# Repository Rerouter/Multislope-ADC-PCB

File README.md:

# Multislope-ADC-PCB
High Resolution Multi-slope ADC Kicad Files

Based on Kleinsteins original design as discussed on the EEVBlog Forum

https://www.eevblog.com/forum/metrology/diy-high-resolution-multi-slope-converter/

https://www.eevblog.com/forum/projects/multislope-design/

The goal of the project is to create a low cost multislope ADC with a useable resolution of 6.5 digits or higher.

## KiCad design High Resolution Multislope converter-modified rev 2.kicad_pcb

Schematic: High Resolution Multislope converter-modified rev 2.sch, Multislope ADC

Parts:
C1, C2, C3, C4, C5, C9, C10, C12, C18, C19, C24, C25, C26, C27, C28, C31, C32, C33, C34, C35, C36, C38, C39, C40, C41, C42, C43, C45, C46, C48, C49, C50, C51, C201, C203, C205, C209, C210: 100n; C_0805_2012Metric
C6: 2.2u; C_0805_2012Metric
C7, C8, C20, C22, C23, C44, C202, C204, C206, C207: 100u; CP_Radial_D8.0mm_P3.50mm
C11: 2.2n; C_Rect_L7.2mm_W3.0mm_P5.00mm_FKS2_FKP2_MKS2_MKP2
C13: 4.7u; C_Rect_L7.2mm_W7.2mm_P5.00mm_FKS2_FKP2_MKS2_MKP2
C14, C21, C29: 220p; C_0805_2012Metric
C15: 22p; C_0805_2012Metric
C16, C47: 10n; C_0805_2012Metric
C17: 330p; C_0805_2012Metric
C30, C37: 1n; C_0805_2012Metric
D1, D7: 12V; D_SOD-323
D3, D5, D8, D11, D12, D13, D14, D18, D19, D201, D202: 1N4148; D_SOD-323
D4, D6, D9: 5.6V; D_SOD-323
D15: BAV199; SOT-23; Manufacturer PArt Number BAV199-7-F; Digikey Part Number BAV199-FDICT-ND
FB1, FB35, FB57, FB102, FB103: Ferrite; L_0805_2012Metric; Manufacturer PArt Number MMZ2012Y152BT
J1: UART; PinHeader_1x04_P2.54mm_Vertical
J2: Input; PinHeader_2x05_P2.54mm_Vertical
J3: ICSP6; PinHeader_2x03_P2.54mm_Vertical
J4: ISCP10; PinHeader_2x05_P2.54mm_Vertical
J5: Power; PinHeader_1x05_P2.54mm_Vertical
LSP6: INTX; PinHeader_1x01_P2.54mm_Vertical
LSP7: Input+; PinHeader_1x01_P2.54mm_Vertical
LSP8: Input-; PinHeader_1x01_P2.54mm_Vertical
LSP200: BIAS; PinHeader_1x01_P2.54mm_Vertical
Q1, Q3, Q4, Q5, Q6, Q9: BC856; SOT-23; Manufacturer PArt Number BC857CLT1G
Q2, Q7, Q8: BC847; SOT-23; Manufacturer PArt Number BC847BLT3G
Q$2: MMBFJ310LT1G; SOT-23; Manufacturer PArt Number MMBFJ310LT1G
R1, R2, R9, R12, R35: 5K; R_0805_2012Metric
R3: 2.2K; R_0805_2012Metric
R4, R11, R37, R52, R63, R68: 1K; R_0805_2012Metric
R5, R6, R16, R24, R36, R45, R48, R49, R55, R65, R69, R71, R72, R73, R90, R91: 22K; R_0805_2012Metric
R7: 100; R_0805_2012Metric
R8: 100K; R_0805_2012Metric
R10: 6.8K; R_0805_2012Metric
R13, R14, R50: 47K; R_0805_2012Metric
R15: 10K; Potentiometer_Vishay_TS53YJ_Vertical
R18, R25, R202: 330K; R_0805_2012Metric
R19, R22, R43, R64, R86, R99: 4.7K; R_0805_2012Metric
R20: 180R; R_0805_2012Metric
R21, R26, R33, R66, R98, R101: 10R; R_0805_2012Metric
R27, R44, R57, R59, R62, R70, R201: 39R; R_0805_2012Metric
R28, R54, R78: 470R; R_0805_2012Metric
R29, R31, R32, R53, R92: 100R; R_0805_2012Metric
R30, R67: OPT; R_0805_2012Metric
R34: 68K; R_0805_2012Metric
R38, R40, R51, R58, R87: 10K; R_0805_2012Metric
R39: 0R; R_0805_2012Metric
R46: 120K; R_0805_2012Metric
R47, R84, R203, R211: Jumper; SolderJumper-2_P1.3mm_Open_RoundedPad1.0x1.5mm
R56: 220K; R_0805_2012Metric
R60: 105K; R_0805_2012Metric
R61: 470K; R_0805_2012Metric
R75, R83: 4.7M; R_0805_2012Metric
R76: 180K; R_0805_2012Metric
R77: 15K; R_0805_2012Metric
R79, R204, R205, R206, R207, R208, R209, R210: 220R; R_0805_2012Metric
R85: 3.3K; R_0805_2012Metric
RN201: 10K; MSOP-8-1EP_3x3mm_P0.65mm_EP1.73x1.85mm
RN202, RN203: 25K; MSOP-8-1EP_3x3mm_P0.65mm_EP1.73x1.85mm
U1, U2, U19: OPA172; SOIC-8_3.9x4.9mm_P1.27mm
U3: 7805; TO-220-3_Vertical
U4: NE5534D; SOIC-8_3.9x4.9mm_P1.27mm; Manufacturer PArt Number NE5534ADR2
U5: 74LV4053; SOIC-16_3.9x9.9mm_P1.27mm
U6: LM399H; TO-46-4; Manufacturer PArt Number LM399H#PBF
U7: DG408DJ; SOIC-16_3.9x9.9mm_P1.27mm; Manufacturer PArt Number DG408DY-T1-E3
U8, U9, U21: OP07CR; SOIC-8_3.9x4.9mm_P1.27mm
U10: LM393; SOIC-8_3.9x4.9mm_P1.27mm; Manufacturer PArt Number LM393DR2G
U11, U12: OPA145; SOIC-8_3.9x4.9mm_P1.27mm
U13: MCP6002; SOIC-8_3.9x4.9mm_P1.27mm; Manufacturer PArt Number MCP6002-E/SN
U14: 7815; TO-220-3_Vertical; Manufacturer PArt Number MC7815ACTG
U15: 7915; TO-220-3_Vertical; Manufacturer PArt Number MC7915CTG
U16: LTC2057; SOIC-8_3.9x4.9mm_P1.27mm; Manufacturer PArt Number LTC2057IS8#PBF
U17: 74HC74; SOIC-14_3.9x8.7mm_P1.27mm
U18: OPA197; SOIC-8_3.9x4.9mm_P1.27mm
U20: DG419LDY; SOIC-8_3.9x4.9mm_P1.27mm; Manufacturer PArt Number DG419DY-E3
U202: MCP4921; SOIC-8_3.9x4.9mm_P1.27mm; Manufacturer PArt Number MCP4821-E/SN
U204: ADuM1201AR; SOIC-8_3.9x4.9mm_P1.27mm; Manufacturer PArt Number ADUM1201ARZ
U$3: ATmega8-16PU; DIP-28_W7.62mm_Socket_LongPads
X1: 16MHz; Oscillator_DIP-14

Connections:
+5V: C4.1, C7.1, C25.1, C205.1, C207.1, D201.1 (K), J3.2, J4.2, Q9.2 (E), R18.1, R21.1, R26.1, R44.2, R66.1, R98.1, R101.1, R201.1, U3.3 (VO), U7.2 (EN), U20.5 (VL), U204.1 (VDD1)
+15V: C33.1, C40.1, C41.1, C42.1, C202.1, C204.1, C206.1, D19.1 (K), Q1.2 (E), Q$2.2 (S), R27.2, R32.2, R33.1, R48.1, R54.2, R56.1, R57.1, R59.2, R62.2, R70.1, R202.2, R203.2, U8.7 (V+), U9.7 (V+), U10.8, U14.3
-15V: C10.2, C19.2, C40.2, C41.2, C42.2, C44.2, C45.2, C48.2, C49.2, C50.2, C51.2, C202.2, C206.2, C209.2, D18.2 (A), R31.2, R45.2, R61.1, R211.2, U6.4 (-), U7.3 (V-), U8.4 (V-), U9.4 (V-), U10.4, U11.4 (V-), U15.3, U16.4 (V-), U18.4 (V-), U19.4 (V-), U21.4 (V-)
/5V_Unreg: C2.1, C8.1, D13.1 (K), D14.1 (K), U3.1 (VI)
/15V_Unreg: C20.1, C32.1, D5.1 (K), D12.1 (K), U14.1
/16MHz: U17.3 (C), U17.11 (C), U$3.9 (PB6/XTAL1), X1.8 (OUT)
/+Ref_In: RN202.3 (R3.1), U5.14 (X); also elsewhere on the board
/-15V_Unreg: C23.2, C34.2, D3.2 (A), D11.2 (A), U15.2
/-Ref_In: RN202.4 (R4.1), U5.15 (Y); also elsewhere on the board
/ADC0: R43.1, U$3.23 (PC0)
/ADC1: R64.1, U$3.24 (PC1)
/AIN0: R34.1, R40.1, U$3.12 (PD6)
/AIN1: C203.1, R15.2, U$3.13 (PD7)
/AREF: C12.1, R36.2, R99.1, U$3.21 (AREF)
/Analog_5V: C3.1, R14.1, R34.2, R98.2, U$3.20 (AVCC)
/Analog_+15V: C9.1, C18.1, C22.1, C43.1, C201.1, R19.1, R28.1, R32.1, U1.7 (V+), U2.7 (V+), U4.7 (V+), U20.4 (V+)
/Analog_-15V: C6.2, C9.2, C18.2, C22.2, C43.2, C201.2, R31.1, R76.2, U1.4 (V-), U2.4 (V-), U4.4 (V-), U20.7 (V-)
/Bootstrap Input: R37.1, U18.3 (+)
/Buffer Input: R63.1, U12.3 (+)
/Buffer_Offset: C31.2, R87.2, U12.6, U19.3 (+)
/Buffer_Output: R52.1, RN203.8 (R1.2), U19.2 (-), U19.6; also elsewhere on the board
/DAC_CS: U202.2 (~CS), U$3.14 (PB0)
/Ext_Input1: J2.7, R35.1, R71.2
/Ext_Input2: J2.5, R72.2
/Ext_Input3: J2.3, R73.2
/Ext_Input4: J2.1, R69.2
/Heater_Setpoint: D202.1 (K), RN202.2 (R2.1), U202.8 (Vout); also elsewhere on the board
/Input1: R71.1, U7.4 (S1)
/Input2: R72.1, U7.5 (S2)
/Input3: R73.1, U7.6 (S3)
/Input4: R69.1, U7.7 (S4)
/Input6: J2.9, R9.1, R90.2, U7.11 (S6)
/Input_Ground: FB35.1, U5.5 (Z0)
/Input_Node: FB103.1, U5.3 (Z1)
/Integrator_Input: C11.1, C14.1, C17.1, C37.1, FB102.2, FB103.2, U2.2 (-), U11.2 (-); also elsewhere on the board
/Integrator_Output: C11.2, Q6.3 (C), R12.2, R83.2, R85.2, U2.6; also elsewhere on the board
/LM399_Zener_Voltage: C210.1, R22.2, R58.2, R91.2, R92.2, R202.1, U6.1 (K)
/MISO: J3.1, J4.9, U$3.18 (PB4)
/MOSI: J3.4, J4.1, U202.4 (SDI), U$3.17 (PB3)
/Mux_Output: R37.2, R63.2, U7.8 (D); also elsewhere on the board
/OC1A: J4.10, R78.1
/OVER: Q9.3 (C), R55.2, U$3.25 (PC2)
/Offset In: R10.2, R11.2, U2.3 (+)
/Offset Out: C14.2, R10.1, R79.2, U11.6
/PC3: R204.1, U7.1 (A0)
/PC4: R205.1, U7.16 (A1)
/PC5: R206.1, U7.15 (A2)
/PD2: R207.1, U5.9 (C)
/PD3: R208.1, U17.12 (D)
/PD3_Sync: U5.10 (B), U17.9 (Q)
/PD4: R209.1, U17.2 (D)
/PD4_Sync: U5.11 (A), U17.5 (Q)
/PD5: R210.1, U20.6
/RX: U204.2 (VOA), U$3.2 (PD0)
/Ref+7V_Unbuffered: C46.1, R92.1, U7.10 (S7)
/Ref_+14V: C26.2, Q7.2 (E), R36.1, R58.1, R91.1, RN201.5 (R4.2), RN203.6 (R3.2); also elsewhere on the board
/Ref_-13.4V: C13.2, C28.2, Q3.2 (E), R8.2, R60.1, R77.1, RN201.8 (R1.1), RN203.5 (R4.2), RN203.7 (R2.2); also elsewhere on the board
/Reference_Ground: FB57.1, U5.2 (Y0), U5.12 (X0)
/Reference_Node: FB102.1, U5.1 (Y1), U5.13 (X1)
/Reset: J3.5, J4.5, U$3.1 (PC6/~RESET)
/SCLK: J3.3, J4.7, U202.3 (SCK), U$3.19 (PB5)
/SS: J4.3, U$3.16 (PB2)
/Sig_In: RN202.1 (R1.1), U5.4 (Z); also elsewhere on the board
/Slope_Input: Q2.1 (B), Q2.2 (E), Q8.3 (C), R12.1, R13.2, U4.2 (-), U20.1
/Slope_Output: Q2.3 (C), Q8.1 (B), Q8.2 (E), R13.1, R24.2, R40.2, U4.6; also elsewhere on the board
/TX: U204.3 (VIB), U$3.3 (PD1)
/Temp: D8.2 (A), R56.2, U7.12 (S5)
/U4_Bal: U4.1 (BAL)
/U4_CB: C15.1, U4.8 (C/B)
/U4_Comp: C15.2, U4.5 (COMP)
/U5_5V: C24.1, R66.2, U5.16 (VDD)
/U5_GND: C24.2, FB1.1, U5.7 (VEE)
/U6_15V: C209.1, Q$2.1 (D), Q$2.3 (G), U6.3 (+)
/U7_15V: C50.1, R62.1, U7.13 (V+)
/U8_FB: C28.1, RN201.6 (R3.1), RN201.7 (R2.2), U8.2 (-); also elsewhere on the board
/U8_Trim 1: U8.1 (VOS)
/U8_Trim 2: U8.8 (VOS)
/U9_FB: C26.1, RN201.3 (R3.2), RN201.4 (R4.1), U9.2 (-); also elsewhere on the board
/U9_Trim 1: U9.1 (VOS)
/U9_Trim 2: U9.8 (VOS)
/U11_15V: C19.1, R33.2, U11.7 (V+)
/U12+: C36.1, D9.1 (K), Q4.3 (C), R49.2, R87.1, U12.7 (V+)
/U12-: C36.2, C47.2, D9.2 (A), R38.1, U12.4 (V-), U18.6
/U12_FB: C31.1, R52.2, U12.2 (-)
/U13A_FB: R24.1, R25.2, U13.2
/U13_5V: C39.1, R44.1, R75.2, U13.8
/U16_15V: C45.1, R57.2, U16.7 (V+)
/U17_5V: C27.1, R26.2, U17.1 (~R), U17.4 (~S), U17.10 (~S), U17.13 (~R), U17.14 (VCC)
/U18_15V: C49.1, R59.1, U18.7 (V+)
/U18_FB: C47.1, R38.2, R49.1, U18.2 (-)
/U19_15V: C48.1, R27.1, U19.7 (V+)
/U21_15V: C51.1, R70.2, U21.7 (V+)
/U202_5V: C5.1, R201.2, U202.1 (Vdd), U202.6 (Vref)
/U301_Trim 1: U21.1 (VOS)
/U301_Trim 2: U21.8 (VOS)
/U$3_5V: C1.1, R21.2, U$3.7 (VCC)
/UART_GND: C38.2, J1.4, U204.5 (GND2)
/UART_RX: J1.3, U204.6 (VOB)
/UART_TX: J1.2, U204.7 (VIA)
/UART_VCC: C38.1, J1.1, U204.8 (VDD2)
/Virtual_Ground: C6.1, FB35.2, FB57.2, R39.2, R47.1
/X1_5V: C35.1, R101.2, X1.14 (Vcc)
/X1_Enable: X1.1 (EN)
GND: C1.2, C2.2, C3.2, C4.2, C5.2, C7.2, C8.2, C10.1, C12.2, C16.2, C20.2, C23.1, C25.2, C27.2, C32.2, C33.2, C34.1, C35.2, C39.2, C44.1, C203.2, C204.2, C205.2, C207.2, D18.1 (K), D19.2 (A), D201.2 (A), D202.2 (A), FB1.2, J3.6, J4.4, J4.6, J4.8, J5.3, R15.1, R16.1, R55.1, R67.2, R84.1, R99.2, U3.2 (GND), U5.6 (INH), U5.8 (VSS), U7.14 (GND), U13.4, U14.2, U15.1, U17.7 (GND), U20.3 (GND), U202.5 (~LDAC), U202.7 (Vss), U204.4 (GND1), U$3.8 (GND), U$3.22 (AGND), X1.7 (GND)
GNDS: C21.2, C29.2, C37.2, C46.2, C210.2, D1.2 (A), D8.1 (K), J2.2, J2.4, J2.6, J2.8, J2.10, R11.1, R20.2, R47.2, R60.2, R77.2, R84.2, RN201.9 (Pad), RN202.9 (Pad), RN203.9 (Pad), U1.3 (+), U4.3 (+), U6.2 (A), U7.9 (S8), U8.3 (+), U11.3 (+), U21.3 (+); also elsewhere on the board
unnamed: C13.1, R22.1, U9.3 (+)
unnamed: C16.1, R75.1, R83.1, U13.5
unnamed: C17.2, R20.1
unnamed: C21.1, D15.1 (A), D15.2 (K), R2.1, R3.2
unnamed: C29.1, R3.1, U16.3 (+)
unnamed: C30.1, R5.2, R6.1, U21.2 (-)
unnamed: C30.2, R6.2, R7.1, R35.2, U21.6
unnamed: D1.1 (K), D7.1 (K)
unnamed: D3.1 (K), D5.2 (A), J5.4, R53.1
unnamed: D4.1 (K), Q7.1 (B), R51.2
unnamed: D4.2 (A), U9.6
unnamed: D6.1 (K), U8.6
unnamed: D6.2 (A), Q3.1 (B), R65.2
unnamed: D11.1 (K), D12.2 (A), J5.2, R29.1
unnamed: D13.2 (A), J5.1, R29.2
unnamed: D14.2 (A), J5.5, R53.2
unnamed: D7.2 (A), D15.3 (common)
unnamed: LSP6.1, R79.1
unnamed: LSP7.1, R1.2
unnamed: LSP8.1, R7.2
unnamed: LSP200.1, R30.2
unnamed: Q1.1 (B), Q4.2 (E), R54.1
unnamed: Q1.3 (C), Q4.1 (B), R61.2
unnamed: Q3.3 (C), R65.1, R211.1
unnamed: Q5.1 (B), Q5.3 (C), Q6.1 (B), R30.1, R76.1
unnamed: Q5.2 (E), R19.2
unnamed: Q6.2 (E), R28.2
unnamed: Q7.3 (C), R51.1, R203.1
unnamed: Q9.1 (B), R50.1
unnamed: R1.1, R2.2
unnamed: R4.1, R5.1, R9.2, U16.6
unnamed: R4.2, U16.2 (-)
unnamed 137: R8.1, RN201.1 (R1.2), RN201.2 (R2.1); also elsewhere on the board
unnamed: R14.2, R15.3
unnamed: R16.2, R18.2, U13.3
unnamed: R25.1, R43.2, U13.1
unnamed: R39.1, U1.2 (-), U1.6
unnamed: R45.1, R46.2, U10.2
unnamed: R46.1, R48.2, U10.5
unnamed: R50.2, U10.1, U10.7
unnamed: R64.2, R68.1, R86.1, U13.7
unnamed: R67.1, R68.2, U13.6
unnamed: R78.2, U$3.15 (PB1)
unnamed: R85.1, U20.2
unnamed: R86.2, U20.8
unnamed: R90.1, U10.3, U10.6
unnamed: R204.2, U$3.26 (PC3)
unnamed: R205.2, U$3.27 (PC4)
unnamed: R206.2, U$3.28 (PC5)
unnamed: R207.2, U$3.4 (PD2)
unnamed: R208.2, U$3.5 (PD3)
unnamed: R209.2, U$3.6 (PD4)
unnamed: R210.2, U$3.11 (PD5)
unnamed 158: RN202.5 (R4.2), RN203.4 (R4.1); also elsewhere on the board
unnamed 159: RN202.6 (R3.2), RN203.3 (R3.1); also elsewhere on the board
unnamed 160: RN202.7 (R2.2), RN203.2 (R2.1); also elsewhere on the board
unnamed 161: RN202.8 (R1.2), RN203.1 (R1.1); also elsewhere on the board

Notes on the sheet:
Input Mux
Microcontroller
16mA
Reference
+-20V
Startup
En - 3100nV
Foil
4.9mW
4.1mW
CRITICAL
12mW
POLY
0.4mW
0.7mW
COG
R60 used to null ground current
+-18V
320Hz BW
2.2mW
183nV En
5pA In - 24.7nV
5K Rn - 161nV
2.1K Rn - 104nV
Tn = 266nV
205nV En
5pA In - 33.2nV
3.75K Rn - 160nV
Tn = 308nV
OPA07 - <500Hz
0.2mW
2.4mW
3.9mW
Microcontroller Null Setpoint
Input Buffer
Communication
Integrator Input Switch
OPA145 - 5.5MHz
Switching at 40-90KHz
iQ 475uA 2.4-3.6mW

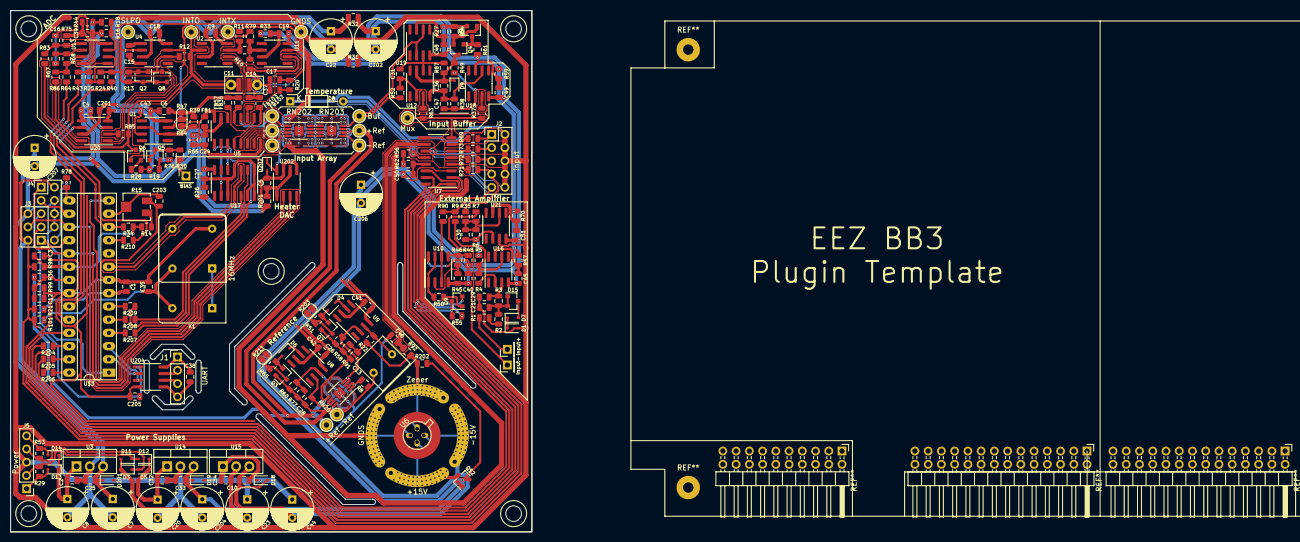
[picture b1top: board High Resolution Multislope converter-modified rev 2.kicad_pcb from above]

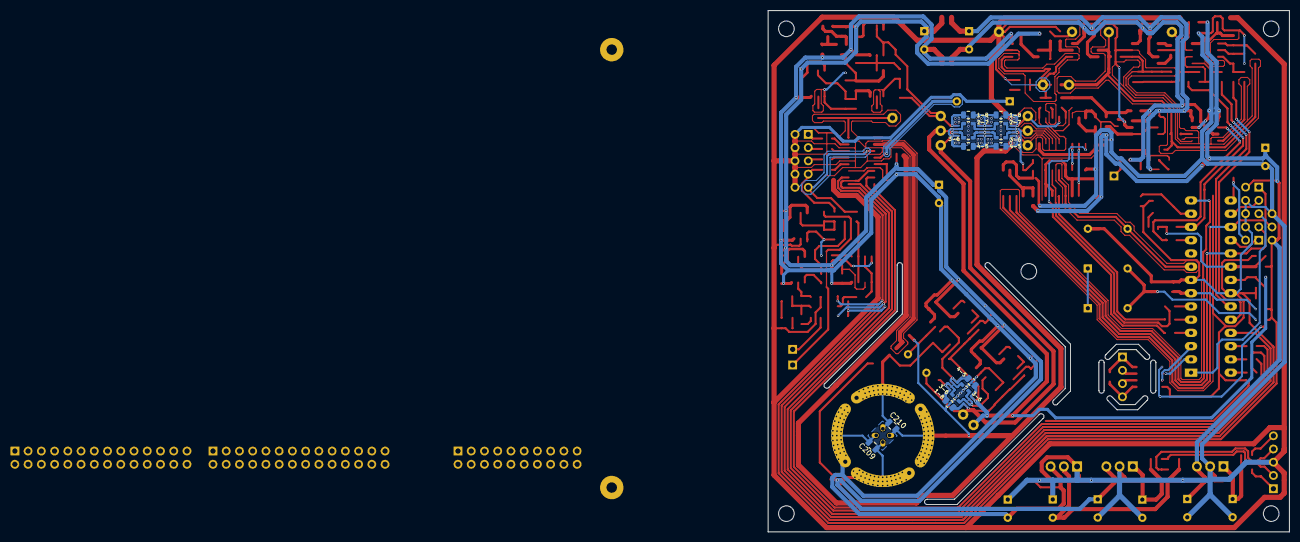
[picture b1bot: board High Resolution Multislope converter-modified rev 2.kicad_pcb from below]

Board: 2 copper layers, 100.0 x 100.0 mm, 250 parts (14 on the bottom side), 154 nets.

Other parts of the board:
1-8, 4-5: 10K; R_0805_2012Metric
1-8#2, 1-8#3, 2-7, 2-7#2, 3-6, 3-6#2, 3-6#3, 3-6#4, 4-5#2, 4-5#3: 20K; R_0805_2012Metric
+Ref: Pin_Header_Straight_1x01_Pitch2.54mm
+Ref#2, +Ref#3: Pin_Header_Straight_1x01_Pitch2.54mm
-Ref: Pin_Header_Straight_1x01_Pitch2.54mm
-Ref#2, -Ref#3: Pin_Header_Straight_1x01_Pitch2.54mm
Buf: Pin_Header_Straight_1x01_Pitch2.54mm
Buf#2: Pin_Header_Straight_1x01_Pitch2.54mm
C11#2: 2.2n; C_Rect_L7.2mm_W3.0mm_P5.00mm_FKS2_FKP2_MKS2_MKP2
GNDS: Pin_Header_Straight_1x01_Pitch2.54mm
INTO: Pin_Header_Straight_1x01_Pitch2.54mm
Mux: Pin_Header_Straight_1x01_Pitch2.54mm
SLPO: Pin_Header_Straight_1x01_Pitch2.54mm

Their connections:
/+Ref_In: 3-6#3.1, +Ref#3.1; also elsewhere on the board
/-Ref_In: 4-5#3.1, -Ref#3.1; also elsewhere on the board
/Buffer_Output: 1-8#2.2, Buf.1; also elsewhere on the board
/Heater_Setpoint: 2-7#2.1; also elsewhere on the board
/Integrator_Input: C11#2.1; also elsewhere on the board
/Integrator_Output: C11#2.2, INTO.1; also elsewhere on the board
/Mux_Output: Mux.1; also elsewhere on the board
/Ref_+14V: 3-6#4.1, 4-5.2, +Ref.1, +Ref#2.1; also elsewhere on the board
/Ref_-13.4V: 1-8.2, 2-7.2, 4-5#2.2, -Ref.1, -Ref#2.1; also elsewhere on the board
/Sig_In: 1-8#3.1, Buf#2.1; also elsewhere on the board
/Slope_Output: SLPO.1; also elsewhere on the board
/U8_FB: 3-6.2, 3-6#2.1; also elsewhere on the board
/U9_FB: 3-6#2.2, 4-5.1; also elsewhere on the board
GNDS: GNDS.1; also elsewhere on the board
unnamed 137: 1-8.1, 3-6.1; also elsewhere on the board
unnamed 158: 4-5#2.1, 4-5#3.2; also elsewhere on the board
unnamed 159: 3-6#3.2, 3-6#4.2; also elsewhere on the board
unnamed 160: 2-7.1, 2-7#2.2; also elsewhere on the board
unnamed 161: 1-8#2.1, 1-8#3.2; also elsewhere on the board

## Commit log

2020-03-22 Initial File Sync
2020-03-23 Added silk screen descriptions
    All test points and through hole points labeled on front and back
    Added test points near to the reference to make it easier to add other references.
2021-09-18 Fix up errors in first fix,
